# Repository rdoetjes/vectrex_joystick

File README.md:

# vectrex_joystick

A small PCB that allows you to connect an arcade style joystick to a vectrex

# manufacturing
You can simply send the vectrext_joystick_for_pcb_manufacturer.zip to your favorite PCB manufacturer and they will print it for you

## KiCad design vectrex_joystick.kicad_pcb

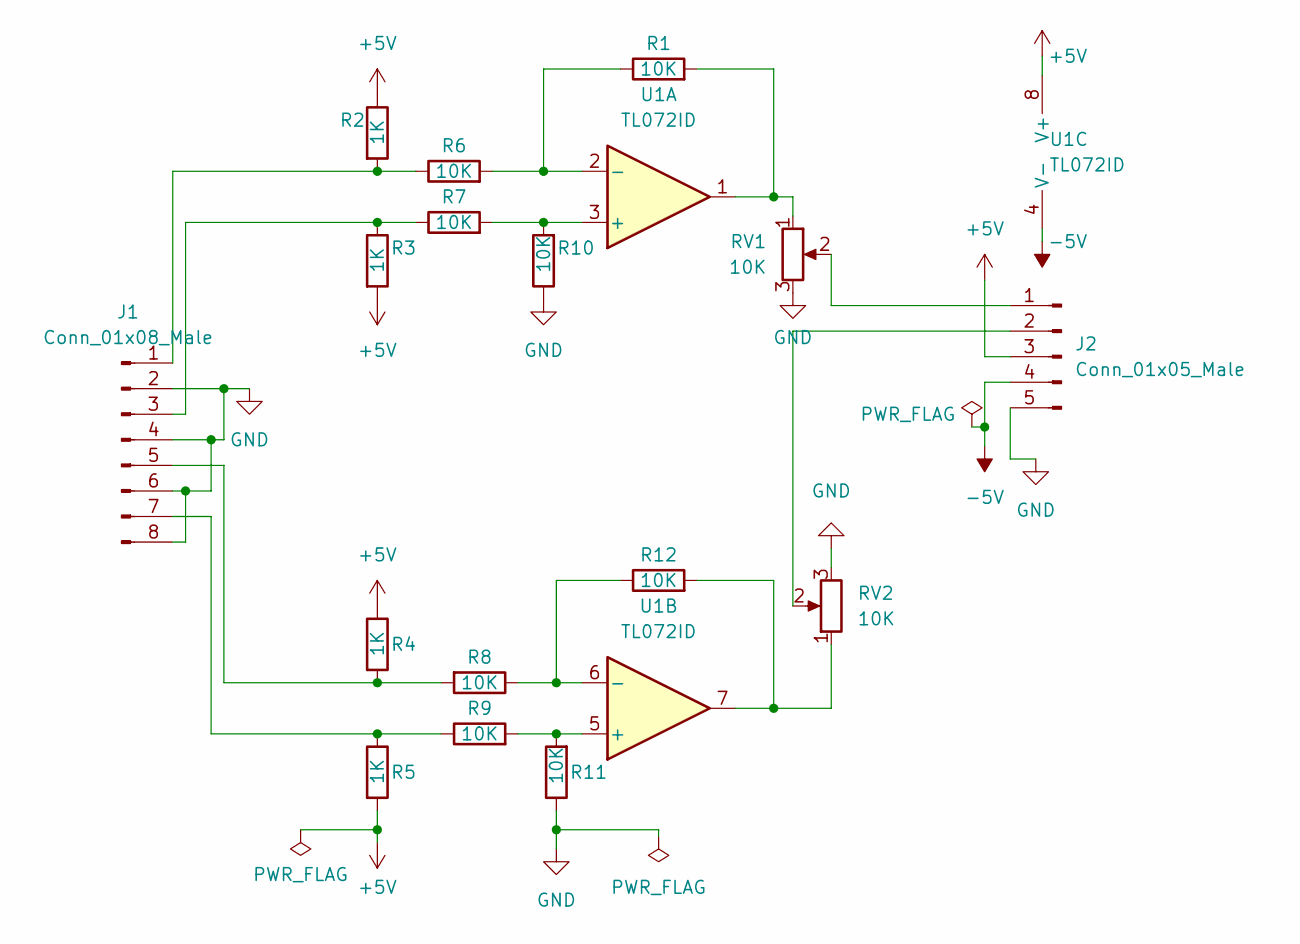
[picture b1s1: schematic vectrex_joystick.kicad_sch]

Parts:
J1: Conn_01x08_Male; PinSocket_1x08_P2.54mm_Vertical
J2: Conn_01x05_Male; PinSocket_1x05_P2.54mm_Vertical
R1, R6, R7, R8, R9, R10, R11, R12: 10K; R_0805_2012Metric_Pad1.20x1.40mm_HandSolder
R2, R3, R4, R5: 1K; R_0805_2012Metric_Pad1.20x1.40mm_HandSolder
RV1, RV2: 10K; Potentiometer_Bourns_3296W_Vertical
U1: TL072ID; SO-8_3.9x4.9mm_P1.27mm

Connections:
+5V: J2.3, R2.1, R3.2, R4.1, R5.2, U1.8 (V+)
-5V: J2.4, U1.4 (V-)
GND: J1.2, J1.4, J1.6, J1.8, J2.5, R10.1, R11.1, RV1.3, RV2.3
unnamed: J1.1, R2.2, R6.1
unnamed: J1.3, R3.1, R7.1
unnamed: J1.5, R4.2, R8.2
unnamed: J1.7, R5.1, R9.1
unnamed: J2.1, RV1.2
unnamed: R1.1, R6.2, U1.2 (-)
unnamed: R1.2, RV1.1, U1.1
unnamed: R7.2, R10.2, U1.3 (+)
unnamed: R9.2, R11.2, U1.5 (+)
unnamed: R8.1, R12.1, U1.6 (-)
unnamed: R12.2, RV2.1, U1.7
unnamed: J2.2, RV2.2

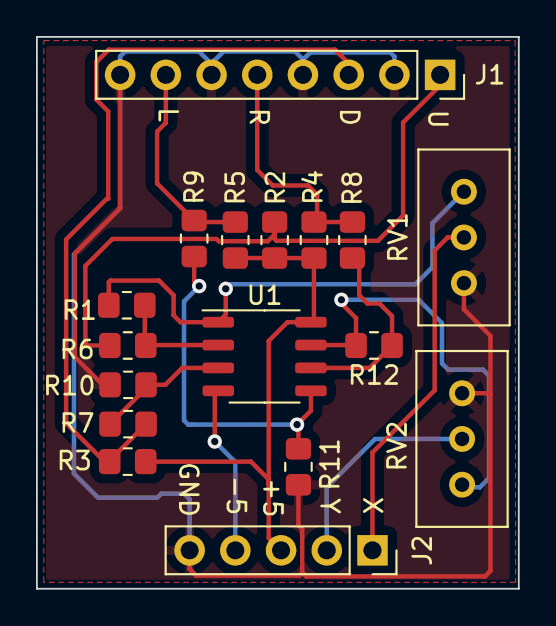
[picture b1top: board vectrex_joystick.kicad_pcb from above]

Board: 2 copper layers, 26.8 x 30.7 mm, 17 parts (0 on the bottom side), 15 nets.

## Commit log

2023-04-08 renamed zip file
